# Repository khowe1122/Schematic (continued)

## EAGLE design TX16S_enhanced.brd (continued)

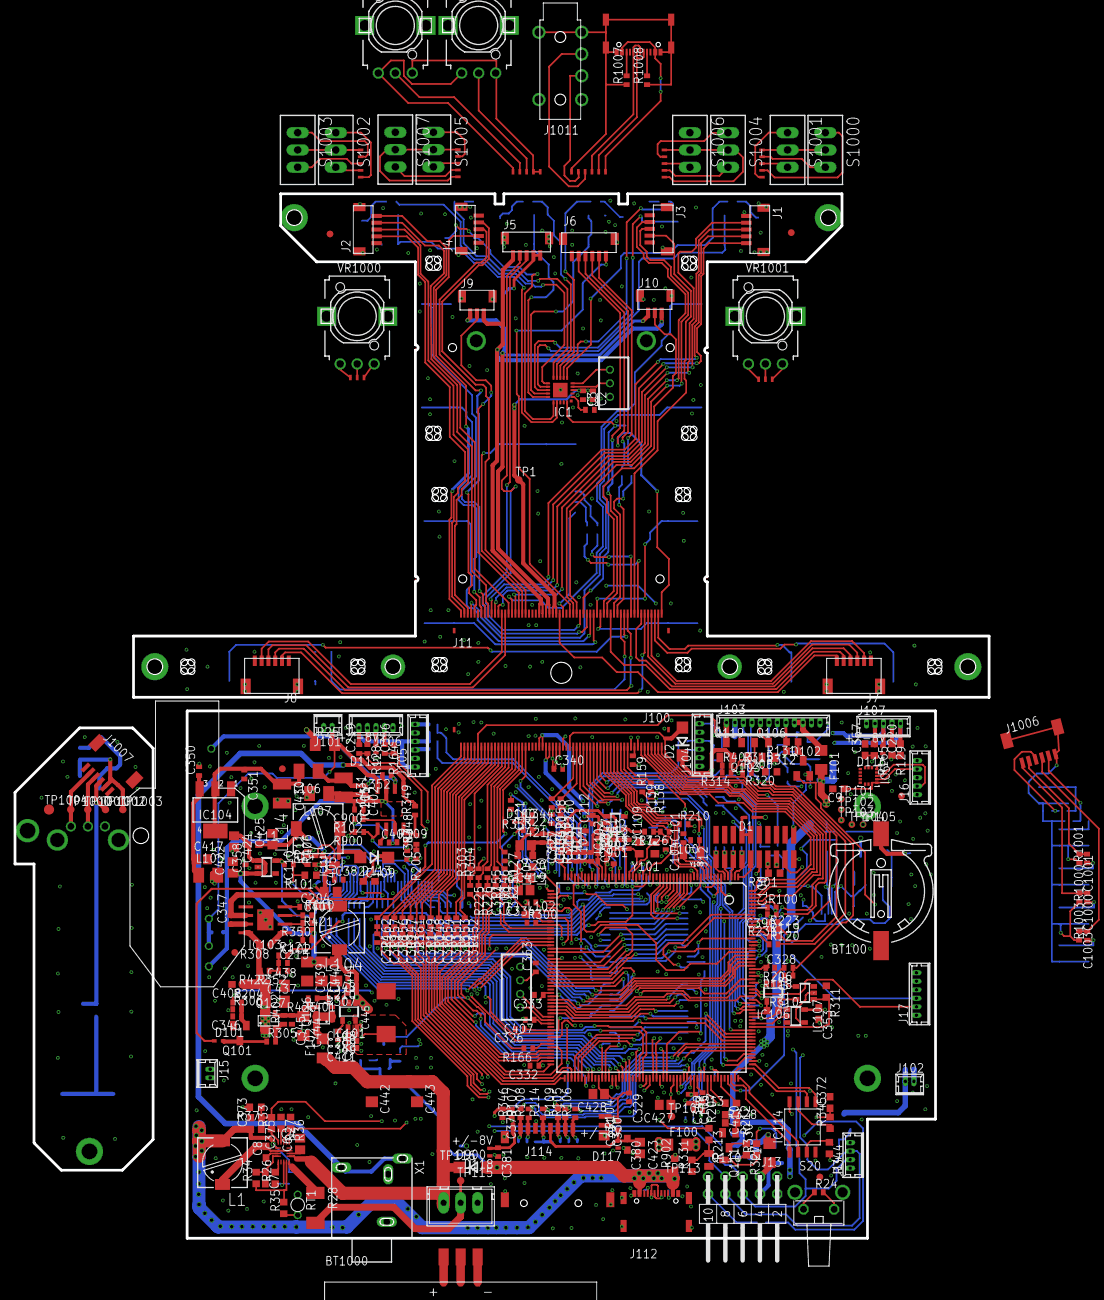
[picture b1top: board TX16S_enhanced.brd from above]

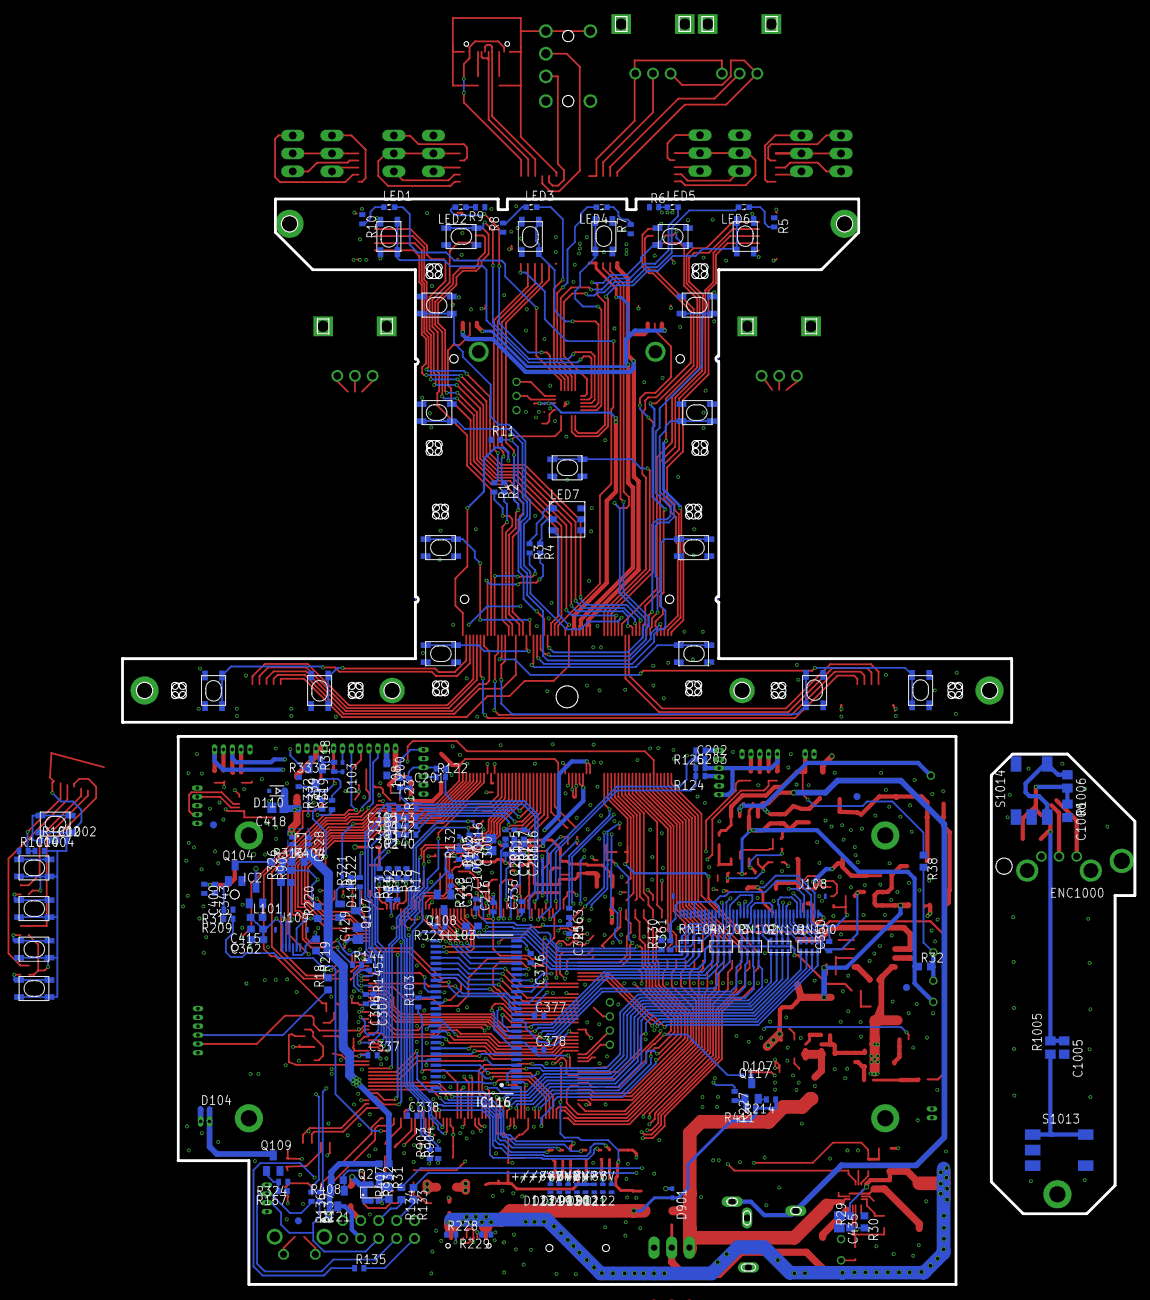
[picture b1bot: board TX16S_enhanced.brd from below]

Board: 4 copper layers, 143.2 x 179.3 mm, 557 parts (192 on the bottom side), 406 nets.
